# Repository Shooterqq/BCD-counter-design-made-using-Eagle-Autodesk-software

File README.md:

# BCD-counter-design-made-using-Eagle-Autodesk-software

It's my project from university. I made BCD counter in Eagle software to projecting PCBs. In effect you can see pfotomask that was next physically made and soldered by me.

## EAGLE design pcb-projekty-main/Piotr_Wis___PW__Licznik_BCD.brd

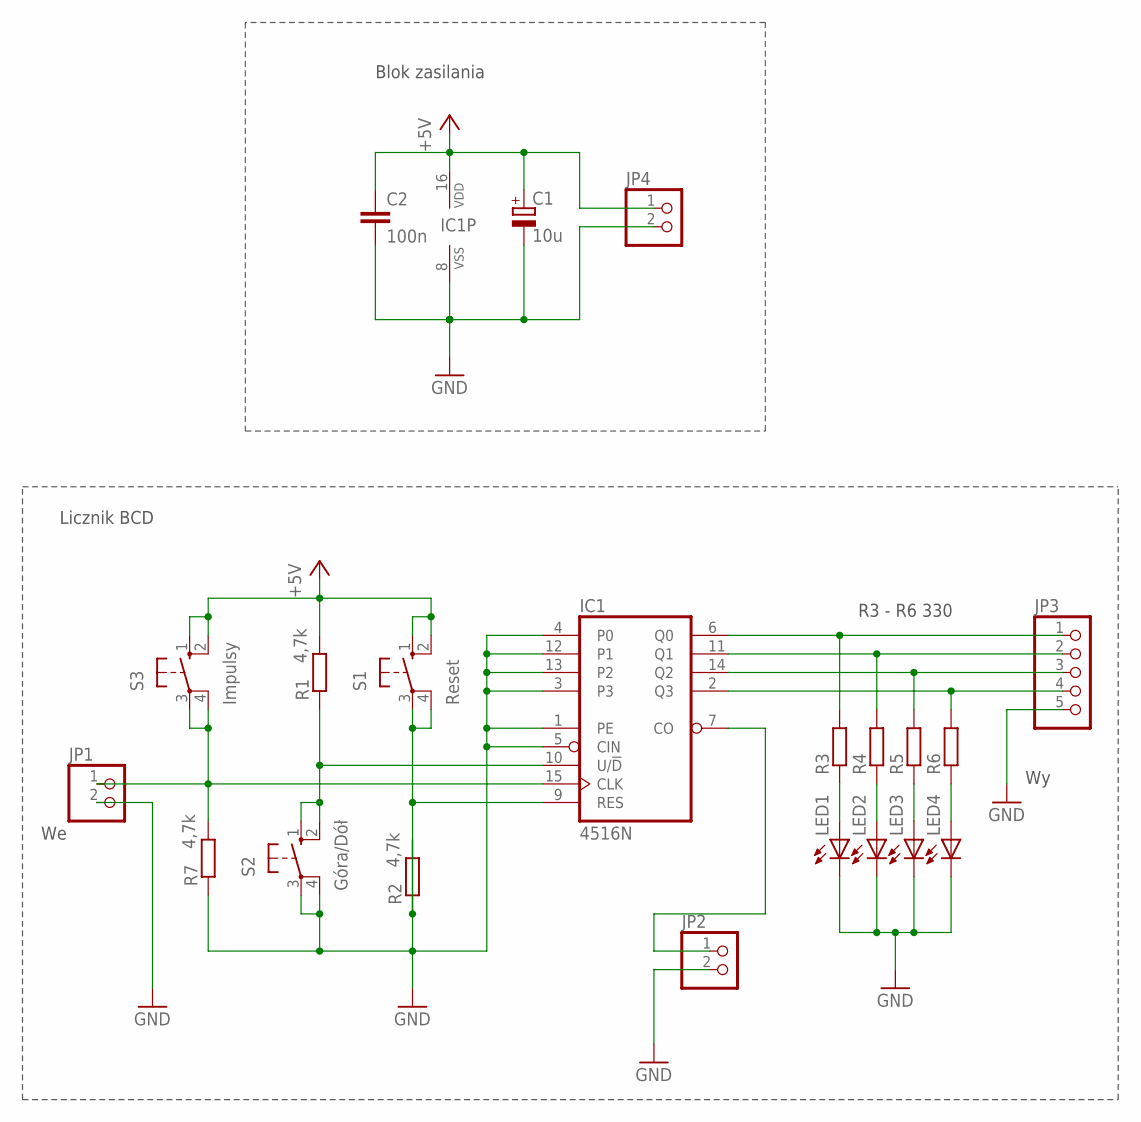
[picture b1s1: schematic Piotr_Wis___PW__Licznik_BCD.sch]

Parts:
C1: 10u; E2,5-6
C2: 100n; C025-025X050
IC1: 4516N; DIL16
JP1, JP2, JP4: PINHD-1X2; 1X02
JP3: PINHD-1X5; 1X05
LED1, LED2, LED3, LED4: LED5MM
R1, R2, R7: 4,7k; R1206
R3, R4, R5, R6: R-EU_0207/10; 0207/10
S1: Reset; B3F-10XX
S2: Góra/Dół; B3F-10XX
S3: Impulsy; B3F-10XX

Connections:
+5V: C1.+, C2.1, IC1.16 (VDD), JP4.1, R1.2, S1.1 (S), S1.2 (S1), S3.1 (S), S3.2 (S1)
GND: C1.-, C2.2, IC1.1 (PE), IC1.3, IC1.4 (P0), IC1.5 (CIN), IC1.8 (VSS), IC1.12 (P1), IC1.13 (P2), JP1.2, JP2.2, JP3.5, JP4.2, LED1.K (C), LED2.K (C), LED3.K (C), LED4.K (C), R2.1, R2.2, R7.1, S2.3, S2.4 (P1)
unnamed: IC1.6 (Q0), JP3.1, R3.2
unnamed: IC1.11 (Q1), JP3.2, R4.2
unnamed: IC1.14 (Q2), JP3.3, R5.2
unnamed: IC1.2 (Q3), JP3.4, R6.2
unnamed: IC1.7 (CO), JP2.1
unnamed: LED4.A, R6.1
unnamed: LED3.A, R5.1
unnamed: LED2.A, R4.1
unnamed: LED1.A, R3.1
unnamed: IC1.15 (CLK), JP1.1, R7.2, S3.3, S3.4 (P1)
unnamed: IC1.9 (RES), S1.3, S1.4 (P1)
unnamed: IC1.10 (U/!D), R1.1, S2.1 (S), S2.2 (S1)

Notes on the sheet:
Licznik BCD
R3 - R6 330
Blok zasilania

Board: 2 copper layers, 21 parts (0 on the bottom side), 14 nets, no tracks yet.

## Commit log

2023-10-05 BCD counter PCB
    BCD counter PCB
